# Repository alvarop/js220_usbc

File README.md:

# Joulescope JS220 USB-C Front Panel

This is a USB-C front panel for the [Joulescope JS220](https://www.joulescope.com/products/js220-joulescope-precision-energy-analyzer)

Here are some renders of what it should look like:

## License
Joulescope JS220 USB-C Front Panel © 2022 by Alvaro Prieto is licensed under CC BY 4.0. To view a copy of this license, visit http://creativecommons.org/licenses/by/4.0/

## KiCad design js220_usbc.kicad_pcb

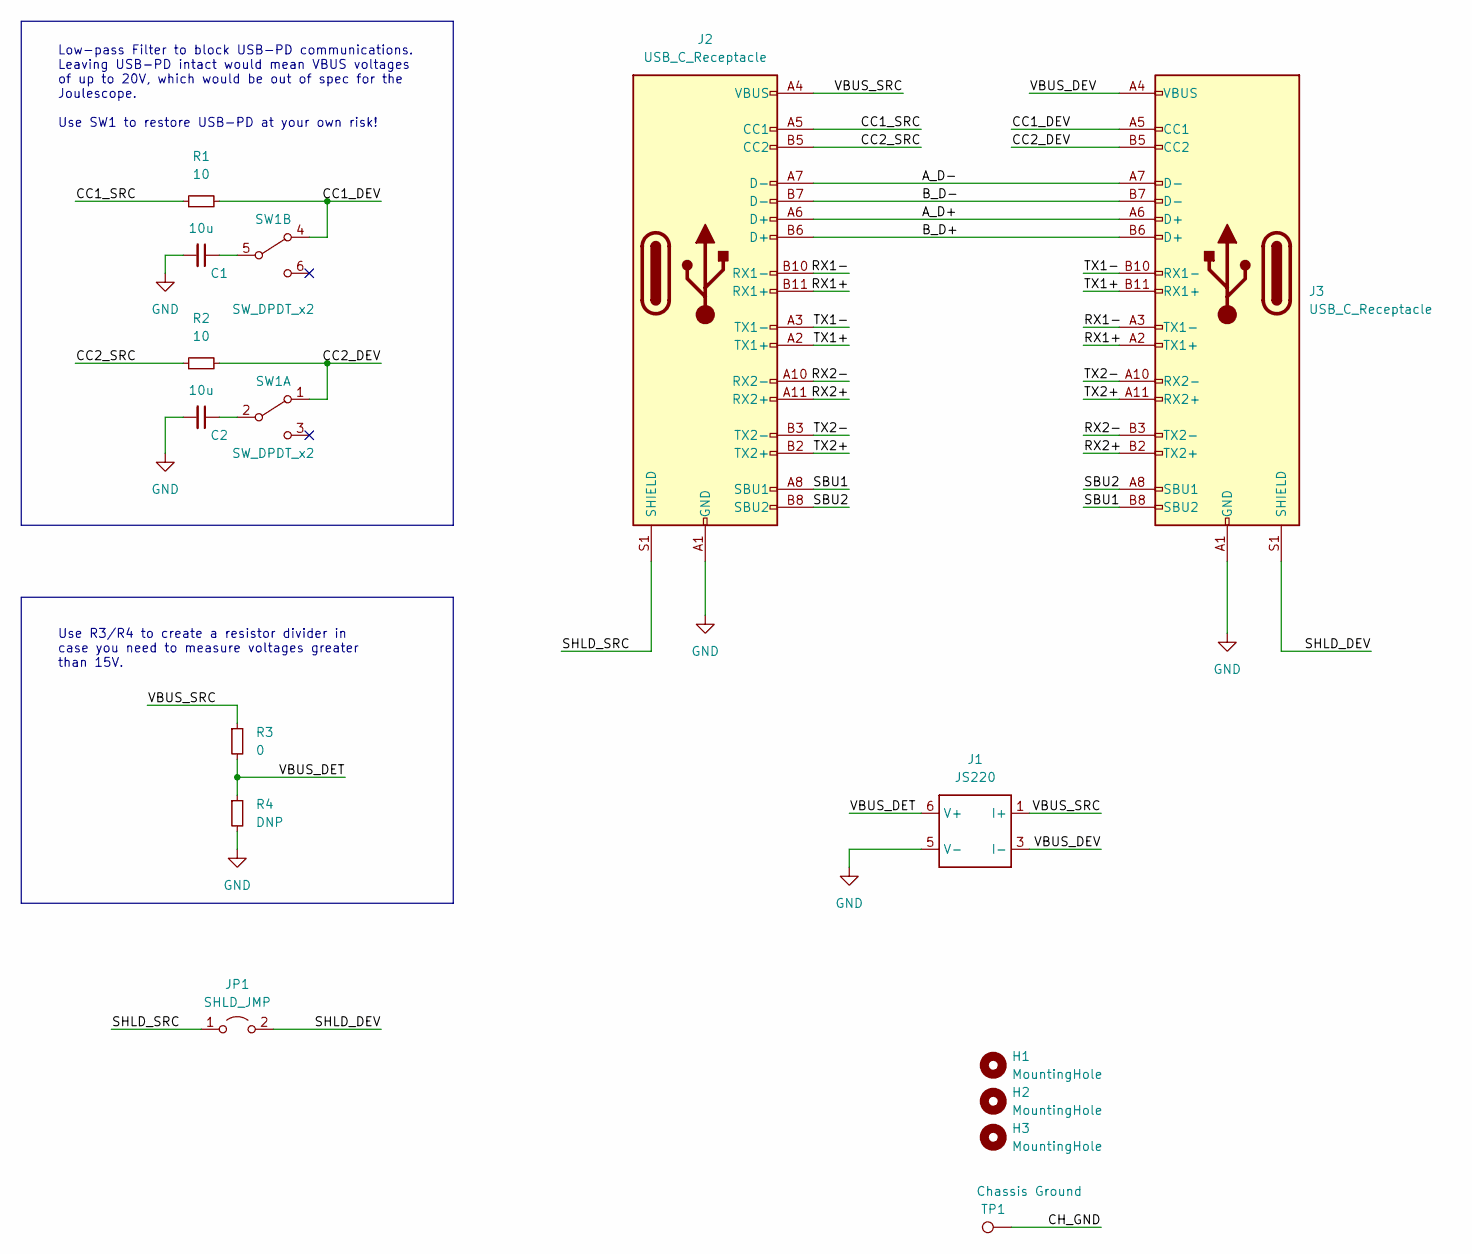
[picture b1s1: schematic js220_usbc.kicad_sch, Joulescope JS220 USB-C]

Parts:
C1, C2: 10u; C_0805_2012Metric
H1, H2: MountingHole; MOUNTING_HOLE_3.5_W_KO
H3: MountingHole; MOUNTING_HOLE_3.3MM
J1: JS220; SAMTEC_TSM-103-01-S-DV-A
J2, J3: USB_C_Receptacle; TYPE-C-31-M-06
JP1: SHLD_JMP; SolderJumper-2_P1.3mm_Open_TrianglePad1.0x1.5mm
R1, R2: 10; R_0603_1608Metric
R3: 0; R_0603_1608Metric
R4: DNP; R_0603_1608Metric
SW1: SW_DPDT_x2; SW_JS202011SCQN
TP1: Chassis Ground; TINY_TP

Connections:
/A_D+: J2.A6 (D+), J3.A6 (D+)
/A_D-: J2.A7 (D-), J3.A7 (D-)
/B_D+: J2.B6 (D+), J3.B6 (D+)
/B_D-: J2.B7 (D-), J3.B7 (D-)
/CC1_DEV: J3.A5 (CC1), R1.2, SW1.4 (A)
/CC1_SRC: J2.A5 (CC1), R1.1
/CC2_DEV: J3.B5 (CC2), R2.2, SW1.1 (A)
/CC2_SRC: J2.B5 (CC2), R2.1
/CH_GND: TP1.1
/RX1+: J2.B11 (RX1+), J3.A2 (TX1+)
/RX1-: J2.B10 (RX1-), J3.A3 (TX1-)
/RX2+: J2.A11 (RX2+), J3.B2 (TX2+)
/RX2-: J2.A10 (RX2-), J3.B3 (TX2-)
/SBU1: J2.A8 (SBU1), J3.B8 (SBU2)
/SBU2: J2.B8 (SBU2), J3.A8 (SBU1)
/SHLD_DEV: J3.S1 (SHIELD), JP1.2 (B)
/SHLD_SRC: J2.S1 (SHIELD), JP1.1 (A)
/TX1+: J2.A2 (TX1+), J3.B11 (RX1+)
/TX1-: J2.A3 (TX1-), J3.B10 (RX1-)
/TX2+: J2.B2 (TX2+), J3.A11 (RX2+)
/TX2-: J2.B3 (TX2-), J3.A10 (RX2-)
/VBUS_DET: J1.6 (V+), R3.2, R4.1
/VBUS_DEV: J1.3 (I-), J1.4 (I-), J3.A4 (VBUS), J3.A9 (VBUS), J3.B4 (VBUS), J3.B9 (VBUS)
/VBUS_SRC: J1.1 (I+), J1.2 (I+), J2.A4 (VBUS), J2.A9 (VBUS), J2.B4 (VBUS), J2.B9 (VBUS), R3.1
GND: C1.2, C2.2, J1.5 (V-), J2.A1 (GND), J2.A12 (GND), J2.B1 (GND), J2.B12 (GND), J3.A1 (GND), J3.A12 (GND), J3.B1 (GND), J3.B12 (GND), R4.2
unnamed: C1.1, SW1.5 (B)
unnamed: C2.1, SW1.2 (B)

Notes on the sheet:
Low-pass Filter to block USB-PD communications. Leaving USB-PD intact would mean VBUS voltages of up to 20V, which would be out of spec for the Joulescope. Use SW1 to restore USB-PD at your own risk!
Use R3/R4 to create a resistor divider in case you need to measure voltages greater than 15V.

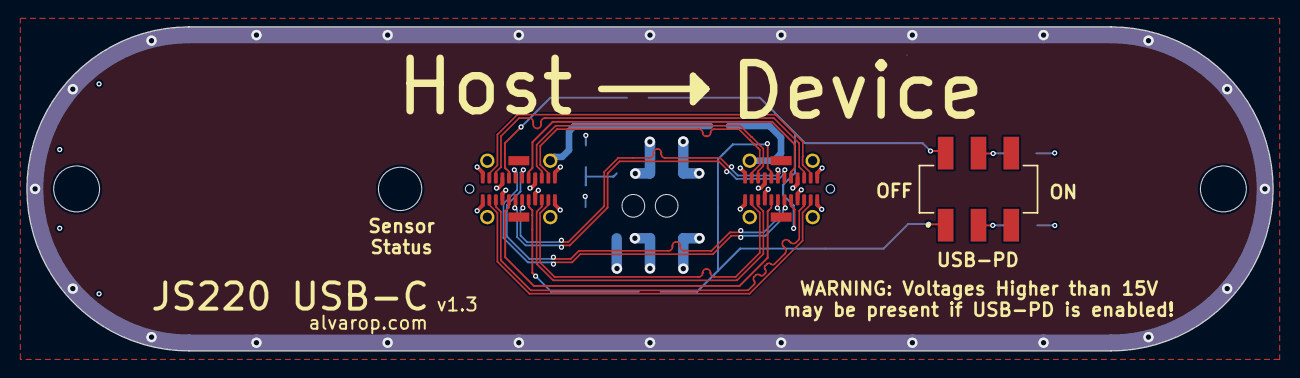
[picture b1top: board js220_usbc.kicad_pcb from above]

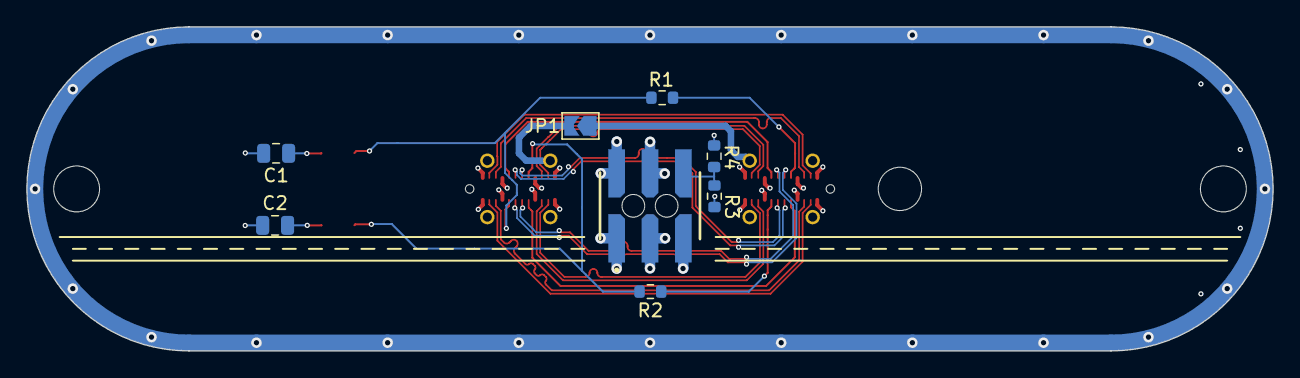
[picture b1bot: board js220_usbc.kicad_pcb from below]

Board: 4 copper layers, 95.0 x 24.7 mm, 15 parts (8 on the bottom side), 26 nets.

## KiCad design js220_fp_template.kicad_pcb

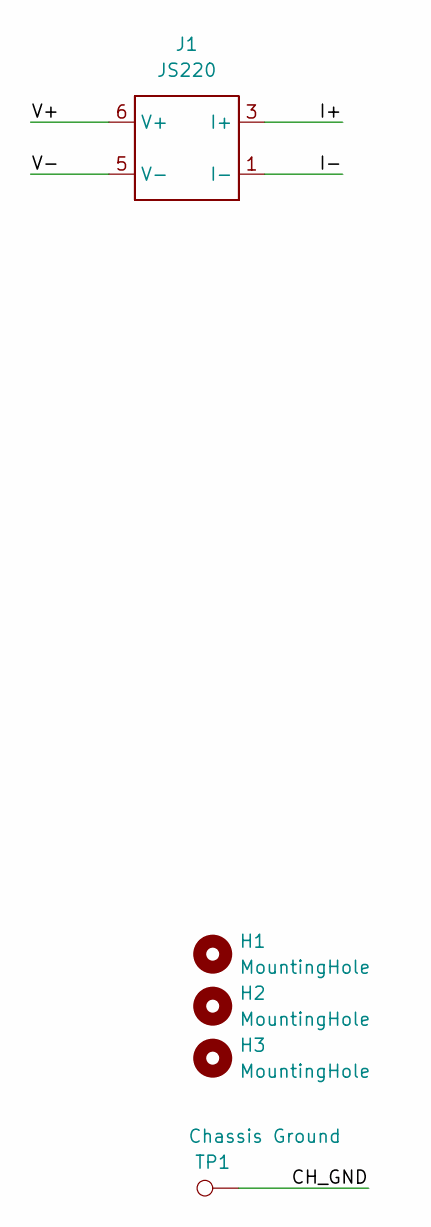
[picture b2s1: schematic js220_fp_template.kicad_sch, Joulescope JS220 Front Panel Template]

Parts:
H1, H2: MountingHole; MOUNTING_HOLE_3.5_W_KO
H3: MountingHole; MOUNTING_HOLE_3.3MM
J1: JS220; SAMTEC_TSM-103-01-S-DV-A
TP1: Chassis Ground; TINY_TP

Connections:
/CH_GND: TP1.1
/I-: J1.1 (I-), J1.2 (I-)
/V+: J1.6 (V+)
/V-: J1.5 (V-)
I+: J1.3 (I+), J1.4 (I+)

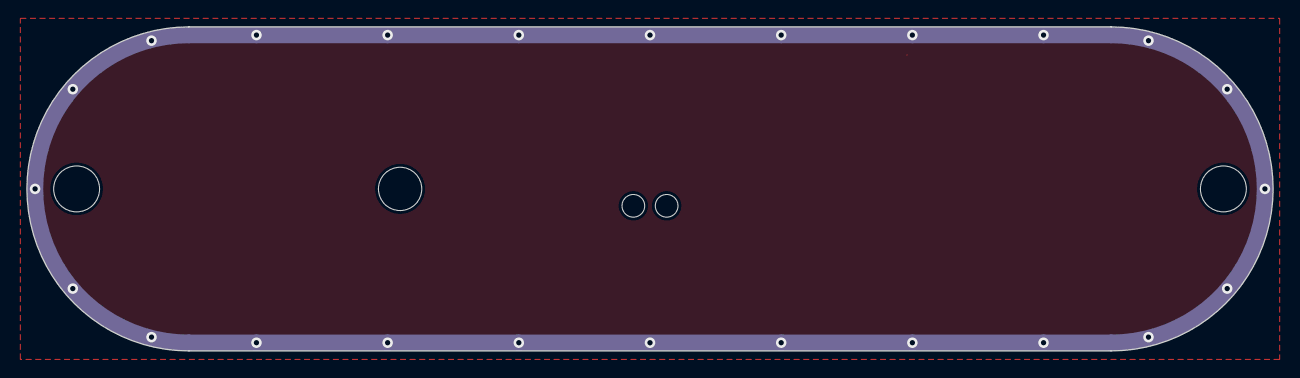
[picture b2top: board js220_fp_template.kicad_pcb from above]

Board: 2 copper layers, 95.0 x 24.7 mm, 5 parts (1 on the bottom side), 2 nets.

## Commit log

2022-10-23 Initial Commit!
2022-10-23 Update to use JS220 symbol and locked PCB items
2022-12-22 Forgot to commit all the files...
2022-12-22 Fix polarity...
2022-12-22 Update readme and silkscreen/version
2023-03-31 v1.2 Done
2023-04-01 Fixed length matching for v1.3
2023-04-01 Adding JLCPCB part table
2023-04-13 Update photos!
